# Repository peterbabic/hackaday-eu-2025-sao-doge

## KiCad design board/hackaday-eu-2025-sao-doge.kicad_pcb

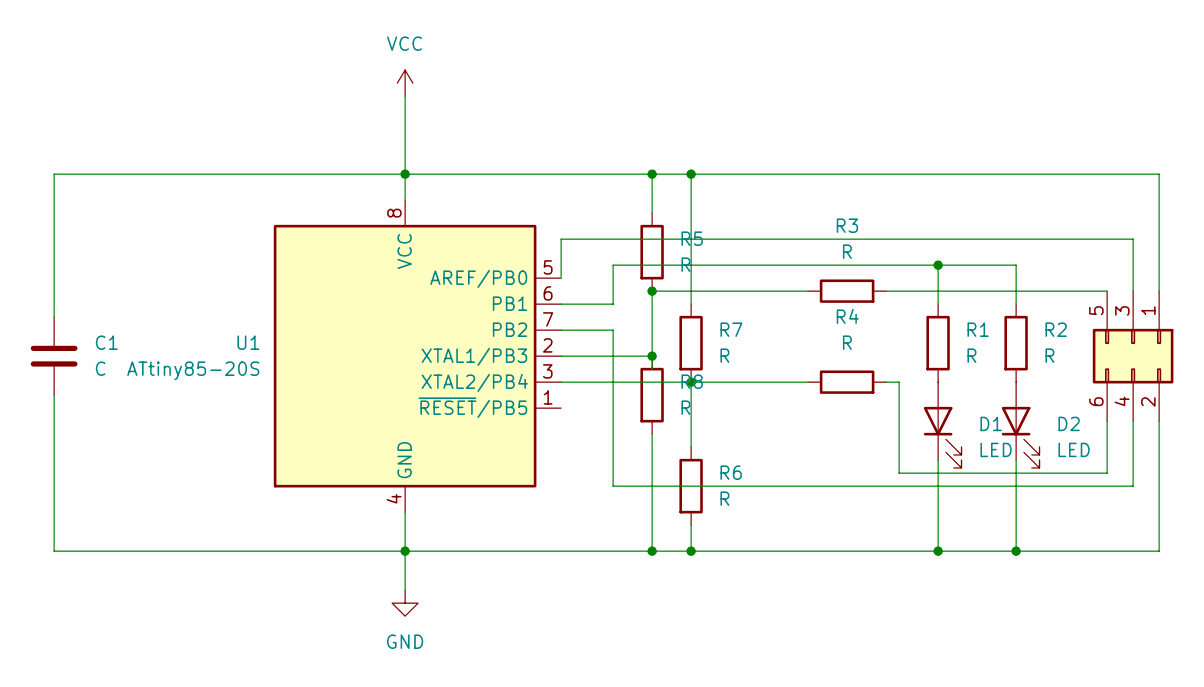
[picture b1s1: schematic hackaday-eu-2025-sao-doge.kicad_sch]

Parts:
C1: C; C_0805_2012Metric_Pad1.18x1.45mm_HandSolder
D1, D2: LED; R_0805_2012Metric_Pad1.20x1.40mm_HandSolder
J2: Conn_02x03_Odd_Even_SAO; PinHeader_2x03_P2.54mm_Vertical
R1, R2, R3, R4, R5, R6, R7, R8: R; R_0805_2012Metric_Pad1.20x1.40mm_HandSolder
U1: ATtiny85-20S; SOIC-8W_5.3x5.3mm_P1.27mm

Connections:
GND: C1.2, D1.1 (K), D2.1 (K), J2.2 (GND), R6.2, R8.2, U1.4 (GND)
unnamed: D1.2 (A), R1.2
unnamed: D2.2 (A), R2.2
unnamed: J2.5 (P1), R3.2
unnamed: J2.6 (P2), R4.2
unnamed: J2.4 (SCL), U1.7 (PB2)
unnamed: J2.3 (SDA), U1.5 (AREF/PB0)
unnamed: R1.1, R2.1, U1.6 (PB1)
unnamed: R3.1, R5.2, R8.1, U1.2 (XTAL1/PB3)
unnamed: R4.1, R6.1, R7.2, U1.3 (XTAL2/PB4)
VCC: C1.1, J2.1 (VCC), R5.1, R7.1, U1.8 (VCC)

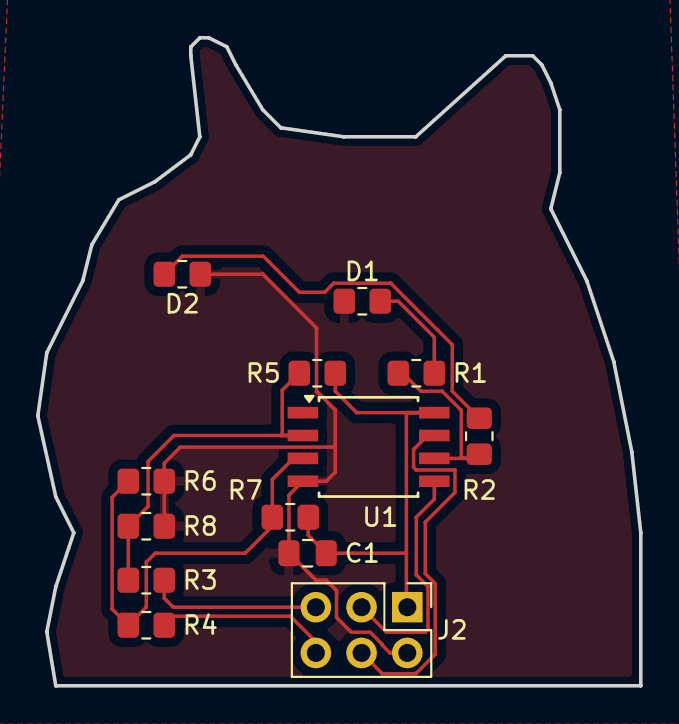
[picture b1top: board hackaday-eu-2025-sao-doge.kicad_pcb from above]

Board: 2 copper layers, 33.5 x 36.0 mm, 13 parts (0 on the bottom side), 11 nets.

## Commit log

2025-02-26 move everything into subfolder
2025-02-26 add blinking
2025-02-27 add fading
2025-02-27 convert to ch341a
2025-03-15 convert back to dragon, ch341a unstable
2025-03-15 add head
2025-03-15 covert to image
2025-03-15 feat: Add Raspberry Pi Pico (RP2040) configuration to platformio.ini
2025-03-15 fix: Add cmsis-dap upload protocol for Raspberry Pi Pico
2025-03-15 add pico into build
2025-03-15 feat: Add Raspberry Pi Pico blink example with separate source file
2025-03-15 feat: Implement synchronized GPIO blinking across multiple pins for Pico
2025-03-15 make all pico gpio blink
2025-03-15 feat: Add fast fade and internal pullup for PB3 button
2025-03-15 feat: Implement button-triggered rapid LED blinking mode
2025-03-15 fix pins
2025-03-15 feat: Modify GPIO control to turn pins on and off sequentially with delays
2025-03-15 add sequence
